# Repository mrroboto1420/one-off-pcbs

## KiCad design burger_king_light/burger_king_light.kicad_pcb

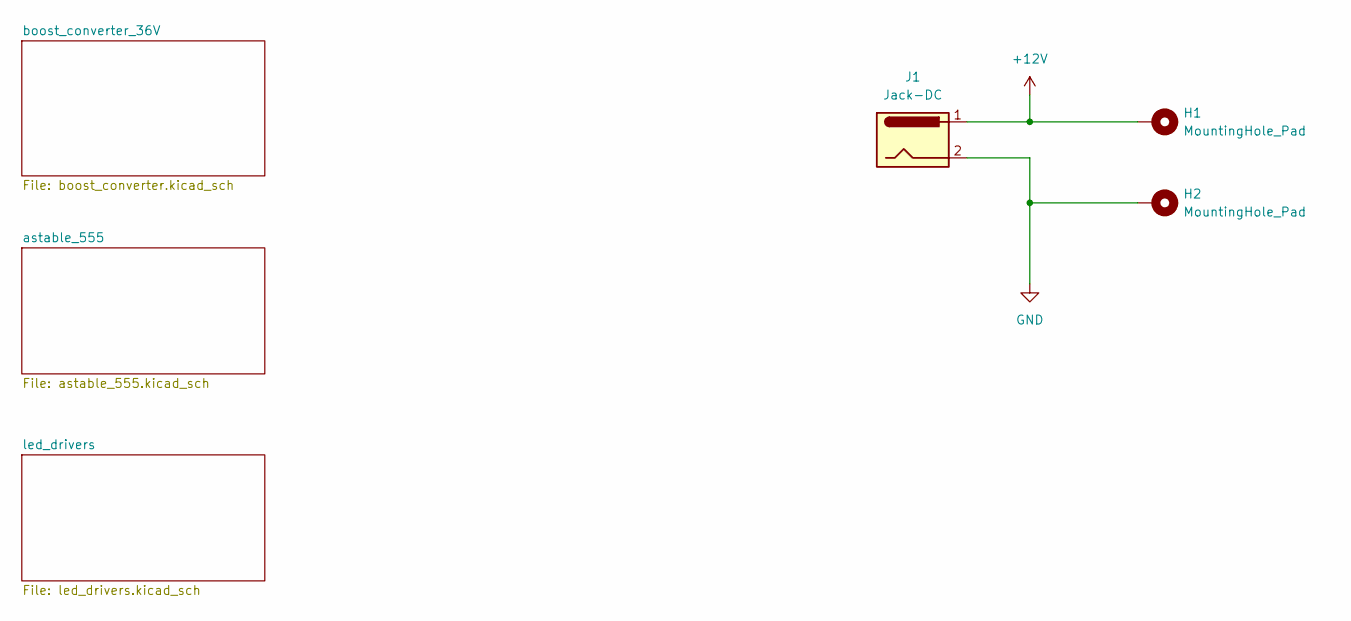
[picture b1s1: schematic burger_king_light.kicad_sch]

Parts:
H1, H2: MountingHole_Pad; MountingHole_2.5mm_Pad_TopBottom
J1: Jack-DC

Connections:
0: H2.1 (1_1), J1.2; also elsewhere on the board
+12V: H1.1 (1_1), J1.1; also elsewhere on the board

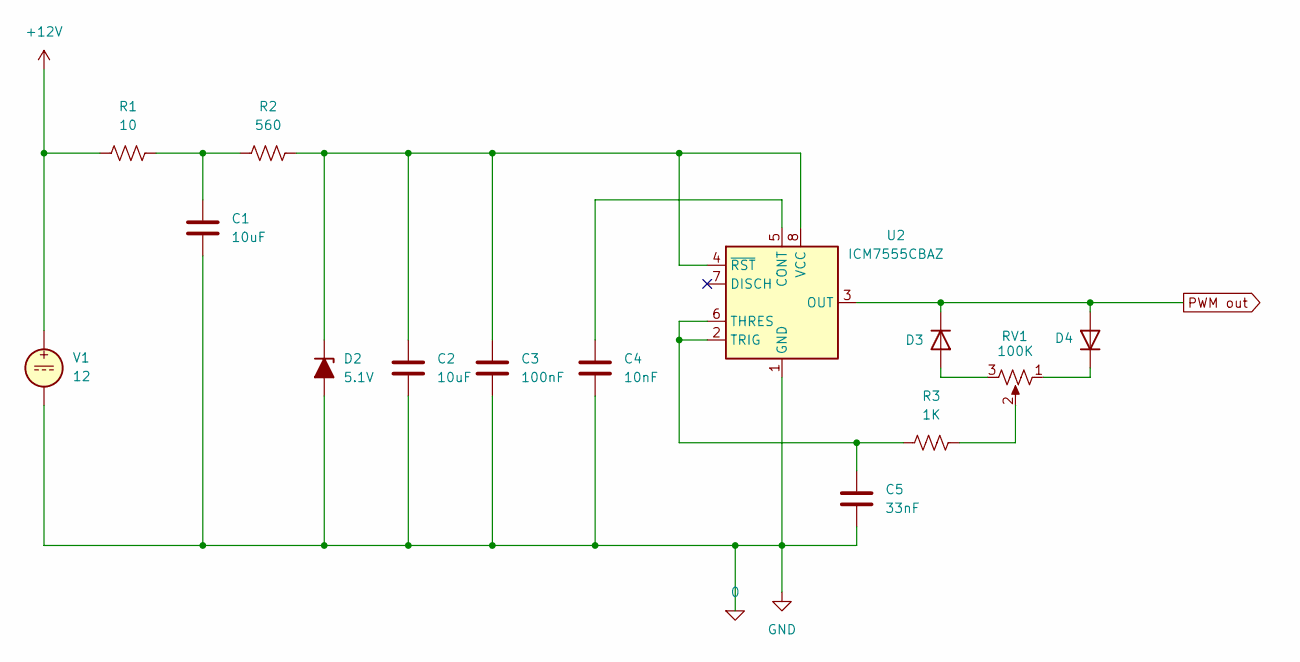
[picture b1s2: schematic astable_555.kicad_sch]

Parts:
C1, C2: 10uF; C_1812_4532Metric; Part Number CGA8P2X7R1E106K250KA
C3: 100nF; C_0805_2012Metric; Part Number 08053C104KAT2A
C4: 10nF; C_1206_3216Metric; Part Number CC1206FKNPO8BN103
C5: 33nF; C_1206_3216Metric; Part Number C1206C333JARECTU
D2: 5.1V; Nexperia_CFP3_SOD-123W; Part Number MMSZ5231B-7-F
D3, D4: 1N4148W; D_SOD-123F
R1: 10; R_1206_3216Metric; Part Number CRM1206-FX-10R0ELF
R2: 560; R_1206_3216Metric; Part Number RK73H2BTTD5600F
R3: 1K; R_1206_3216Metric; Part Number RC1206FR-071KL
RV1: 100K; 3-PIN POT; Part Number 270X232A104B1A1
U2: ICM7555CBAZ; SOIC-8_3.9x4.9mm_P1.27mm
V1: 12

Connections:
0: C1.2, C2.2, C3.2, C4.1, C5.2, D2.2 (A), U2.1 (GND), V1.2; also elsewhere on the board
+12V: R1.1, V1.1; also elsewhere on the board
unnamed: C1.1, R1.2, R2.1
unnamed: C2.1, C3.1, D2.1 (K), R2.2, U2.4 (~RST), U2.8 (VCC)
unnamed: D3.2 (A), RV1.3
unnamed: D4.1 (K), RV1.1
unnamed: R3.2, RV1.2
unnamed: C4.2, U2.5 (CONT)
unnamed: C5.1, R3.1, U2.2 (TRIG), U2.6 (THRES)
PWM out: D3.1 (K), D4.2 (A), U2.3 (OUT); also elsewhere on the board

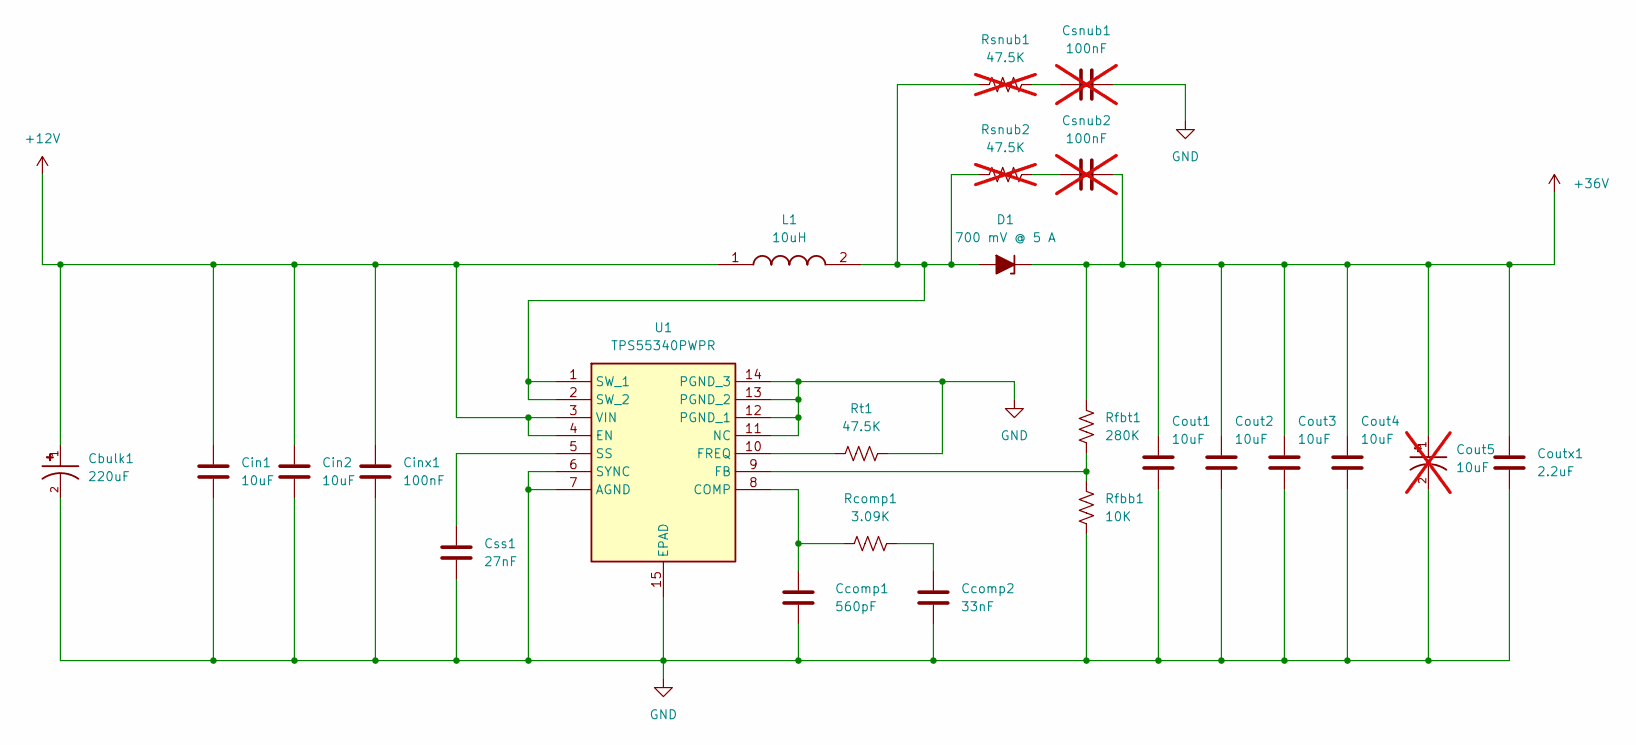
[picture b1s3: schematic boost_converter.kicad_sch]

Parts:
Cbulk1: 220uF; CP_Radial_D8.0mm_P3.50mm
Ccomp1: 560pF; C_1206_3216Metric; Part Number KGM31BCG2A561JT
Ccomp2: 33nF; C_1206_3216Metric; Part Number C1206C333F5GEC7210
Cin1, Cin2: 10uF; C_1812_4532Metric; Part Number C1812X106K050T
Cinx1: 100nF; C_0805_2012Metric; Part Number 08053C104KAT2A
Cout1, Cout2, Cout3, Cout4: 10uF; C_1812_4532Metric; Part Number C1812X106K050T
Cout5: 10uF; CP_Elec_5x5.3; PARTREV 30-Sep-20; not fitted
Coutx1: 2.2uF; C_0805_2012Metric; Part Number C2012X5R1H225K125AB
Csnub1, Csnub2: 100nF; C_0805_2012Metric; Part Number 08053C104KAT2A; not fitted
Css1: 27nF; C_1206_3216Metric; Part Number KGM31BR72A273KT
D1: 700 mV @ 5 A; D_SMC; Part Number B560CQ-13-F
L1: 10uH; INDPM125125X450N; Mouser Part Number 542-PM124SH-100M-RC
Rcomp1: 3.09K; R_1206_3216Metric; Part Number ERA-8AEB3091V
Rfbb1: 10K; R_1206_3216Metric; Part Number CRCW120610K0FKEA
Rfbt1: 280K; R_1206_3216Metric; Part Number RQ73C2B280KBTD
Rsnub1, Rsnub2: 47.5K; R_1206_3216Metric; Part Number CRCW120647K5FKEA; not fitted
Rt1: 47.5K; R_1206_3216Metric; Part Number CRCW120647K5FKEA
U1: TPS55340PWPR; SOP65P640X120-15N; Mouser Part Number 595-TPS55340PWPR

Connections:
0: Cbulk1.2, Ccomp1.2, Ccomp2.2, Cin1.2, Cin2.2, Cinx1.2, Cout1.2, Cout2.2, Cout3.2, Cout4.2, Cout5.2, Coutx1.2, Csnub1.2, Css1.2, Rfbb1.2, Rt1.1, U1.6 (SYNC), U1.7 (AGND), U1.11 (NC), U1.12 (PGND_1), U1.13 (PGND_2), U1.14 (PGND_3), U1.15 (EPAD); also elsewhere on the board
+12V: Cbulk1.1, Cin1.1, Cin2.1, Cinx1.1, L1.1, U1.3 (VIN), U1.4 (EN); also elsewhere on the board
+36V: Cout1.1, Cout2.1, Cout3.1, Cout4.1, Cout5.1, Coutx1.1, Csnub2.2, D1.1 (K), Rfbt1.1; also elsewhere on the board
unnamed: Ccomp2.1, Rcomp1.2
unnamed: Csnub1.1, Rsnub1.1
unnamed: Csnub2.1, Rsnub2.1
unnamed: D1.2 (A), L1.2, Rsnub1.2, Rsnub2.2, U1.1 (SW_1), U1.2 (SW_2)
unnamed: Ccomp1.1, Rcomp1.1, U1.8 (COMP)
unnamed: Rfbb1.1, Rfbt1.2, U1.9 (FB)
unnamed: Rt1.2, U1.10 (FREQ)
unnamed: Css1.1, U1.5 (SS)

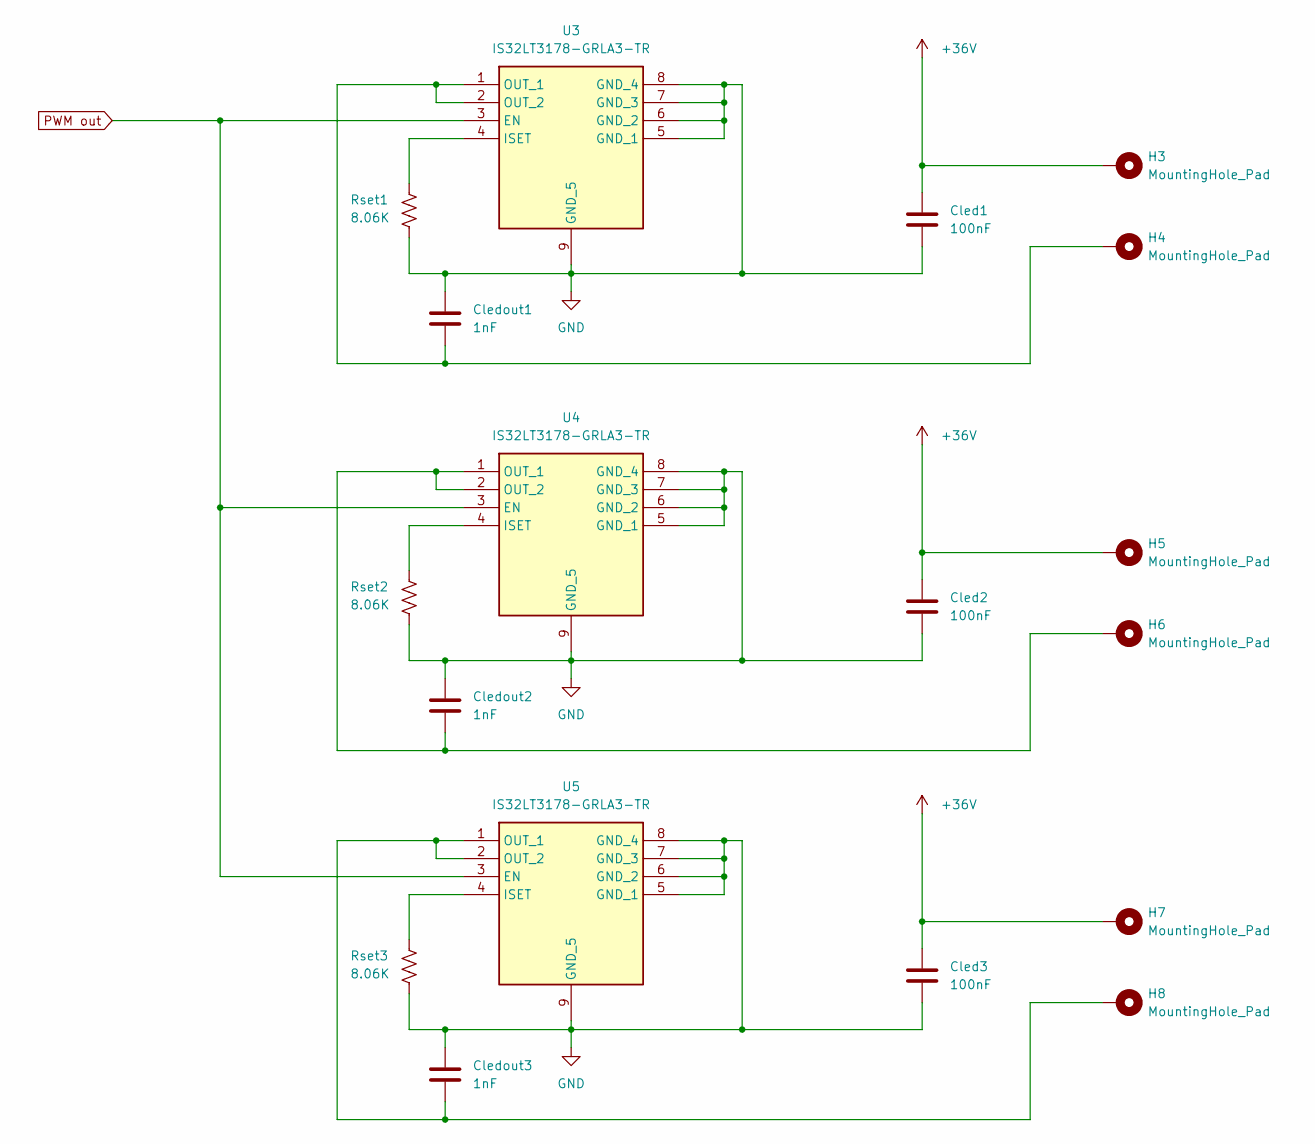
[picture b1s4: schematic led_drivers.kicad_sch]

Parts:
Cled1, Cled2, Cled3: 100nF; C_0805_2012Metric; Part Number 08053C104KAT2A
Cledout1, Cledout2, Cledout3: 1nF; C_0805_2012Metric; Part Number C0805C102J5GACTU
H3, H4, H5, H6, H7, H8: MountingHole_Pad; MountingHole_2.5mm_Pad_TopBottom
Rset1, Rset2, Rset3: 8.06K; R_1206_3216Metric; Part Number RK73H2BTTD8061F
U3, U4, U5: IS32LT3178-GRLA3-TR; SOIC127P600X170-9N; Mouser Part Number 870-3177-GRLA3-TR

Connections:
0: Cled1.2, Cled2.2, Cled3.2, Cledout1.2, Cledout2.2, Cledout3.2, Rset1.2, Rset2.2, Rset3.2, U3.5 (GND_1), U3.6 (GND_2), U3.7 (GND_3), U3.8 (GND_4), U3.9 (GND_5), U4.5 (GND_1), U4.6 (GND_2), U4.7 (GND_3), U4.8 (GND_4), U4.9 (GND_5), U5.5 (GND_1), U5.6 (GND_2), U5.7 (GND_3), U5.8 (GND_4), U5.9 (GND_5); also elsewhere on the board
+36V: Cled1.1, Cled2.1, Cled3.1, H3.1 (1_1), H5.1 (1_1), H7.1 (1_1); also elsewhere on the board
unnamed: Rset1.1, U3.4 (ISET)
unnamed: Cledout1.1, H4.1 (1_1), U3.1 (OUT_1), U3.2 (OUT_2)
unnamed: Rset2.1, U4.4 (ISET)
unnamed: Cledout2.1, H6.1 (1_1), U4.1 (OUT_1), U4.2 (OUT_2)
unnamed: Rset3.1, U5.4 (ISET)
unnamed: Cledout3.1, H8.1 (1_1), U5.1 (OUT_1), U5.2 (OUT_2)
PWM out: U3.3 (EN), U4.3 (EN), U5.3 (EN); also elsewhere on the board

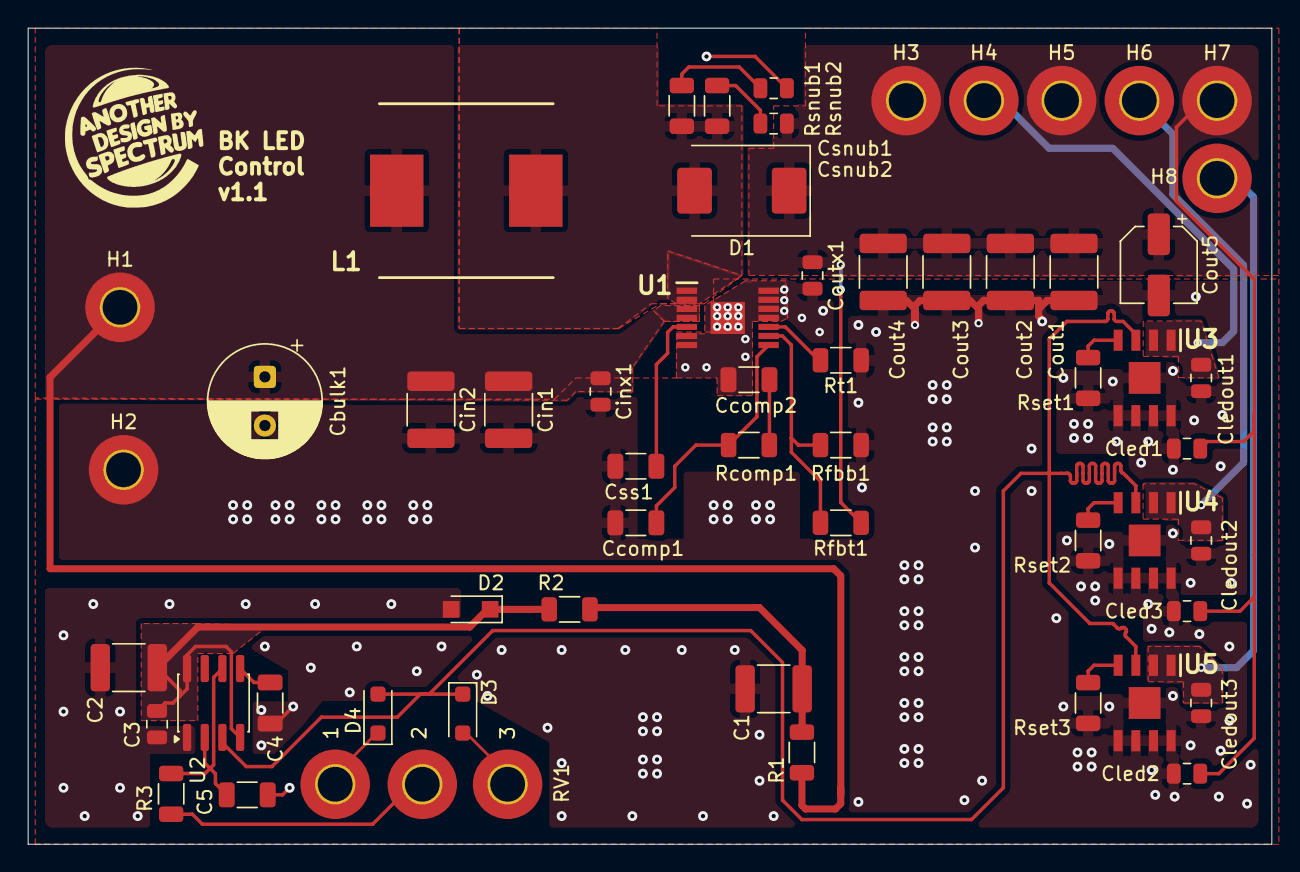
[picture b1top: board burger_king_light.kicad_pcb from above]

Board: 2 copper layers, 89.4 x 58.7 mm, 57 parts (0 on the bottom side), 25 nets.
